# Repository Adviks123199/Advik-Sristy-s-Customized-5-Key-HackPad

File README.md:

# Advik-Sristy-s-Customized-5-Key-HackPad

I created this 5-key macropad, which features an ergonomic layout for fingers to reach the keys with ease. It also features a status LED, along with a capacitor.

Challenges:
I had a difficult time with the proportions and getting them right because KiCAD threw me off by so much.

Total time: 
It took me the entire long weekend to do this.

BOM:
-   x1 Microcontroller	Seeed Studio XIAO RP2040
-   x5 Switches	Cherry MX Style Switches
-   x1 SK6812 MINI LED
-   x5 Blank Keycaps	1u MX-compatible Keycaps
-   x4 M3x16 Bolt
-   x4 M3 Heatset
-   x1 roll of Solder(tin/lead)
-   x1 Soldering Iron

CASE TOP AND BOTTOM

SCHEMATIC                                          

PCB

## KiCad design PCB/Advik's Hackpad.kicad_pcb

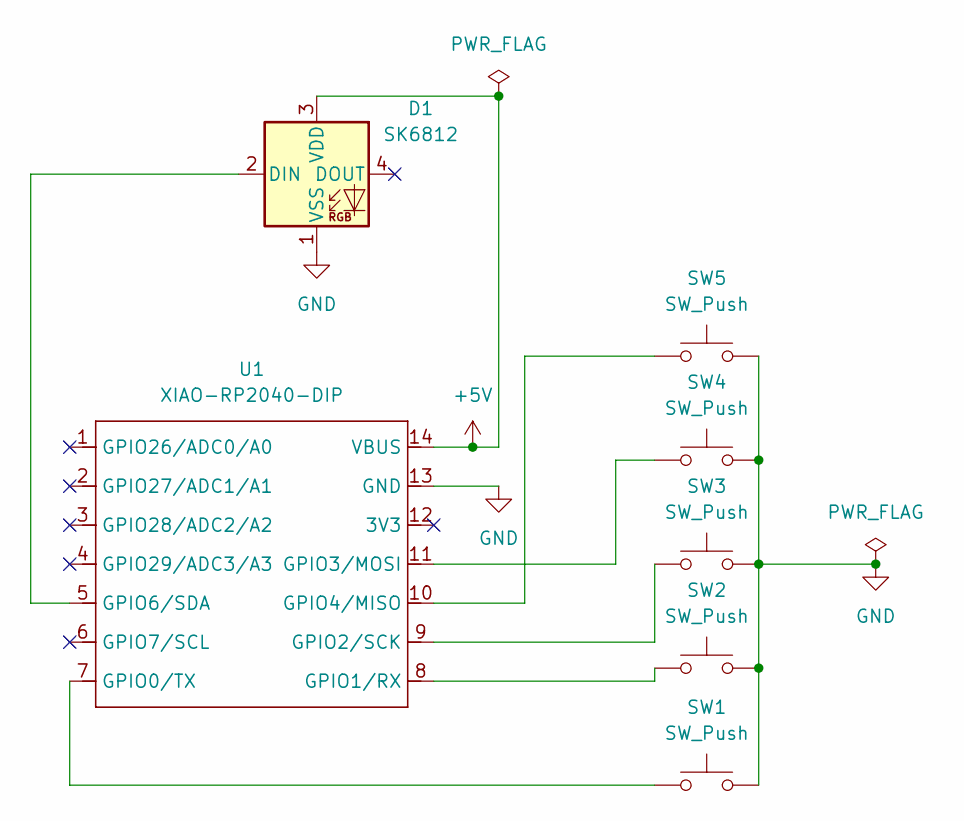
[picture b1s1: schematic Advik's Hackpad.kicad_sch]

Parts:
D1: SK6812; LED_SK6812MINI_PLCC4_3.5x3.5mm_P1.75mm
SW1, SW2, SW3, SW4, SW5: SW_Push; SW_Cherry_MX_1.00u_PCB
U1: XIAO-RP2040-DIP

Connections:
+5V: D1.3 (VDD), U1.14 (VBUS)
GND: D1.1 (VSS), SW1.2, SW2.2, SW3.2, SW4.2, SW5.2, U1.13 (GND)
unnamed: D1.2 (DIN), U1.5 (GPIO6/SDA)
unnamed: SW1.1, U1.7 (GPIO0/TX)
unnamed: SW2.1, U1.8 (GPIO1/RX)
unnamed: SW3.1, U1.9 (GPIO2/SCK)
unnamed: SW4.1, U1.11 (GPIO3/MOSI)
unnamed: SW5.1, U1.10 (GPIO4/MISO)

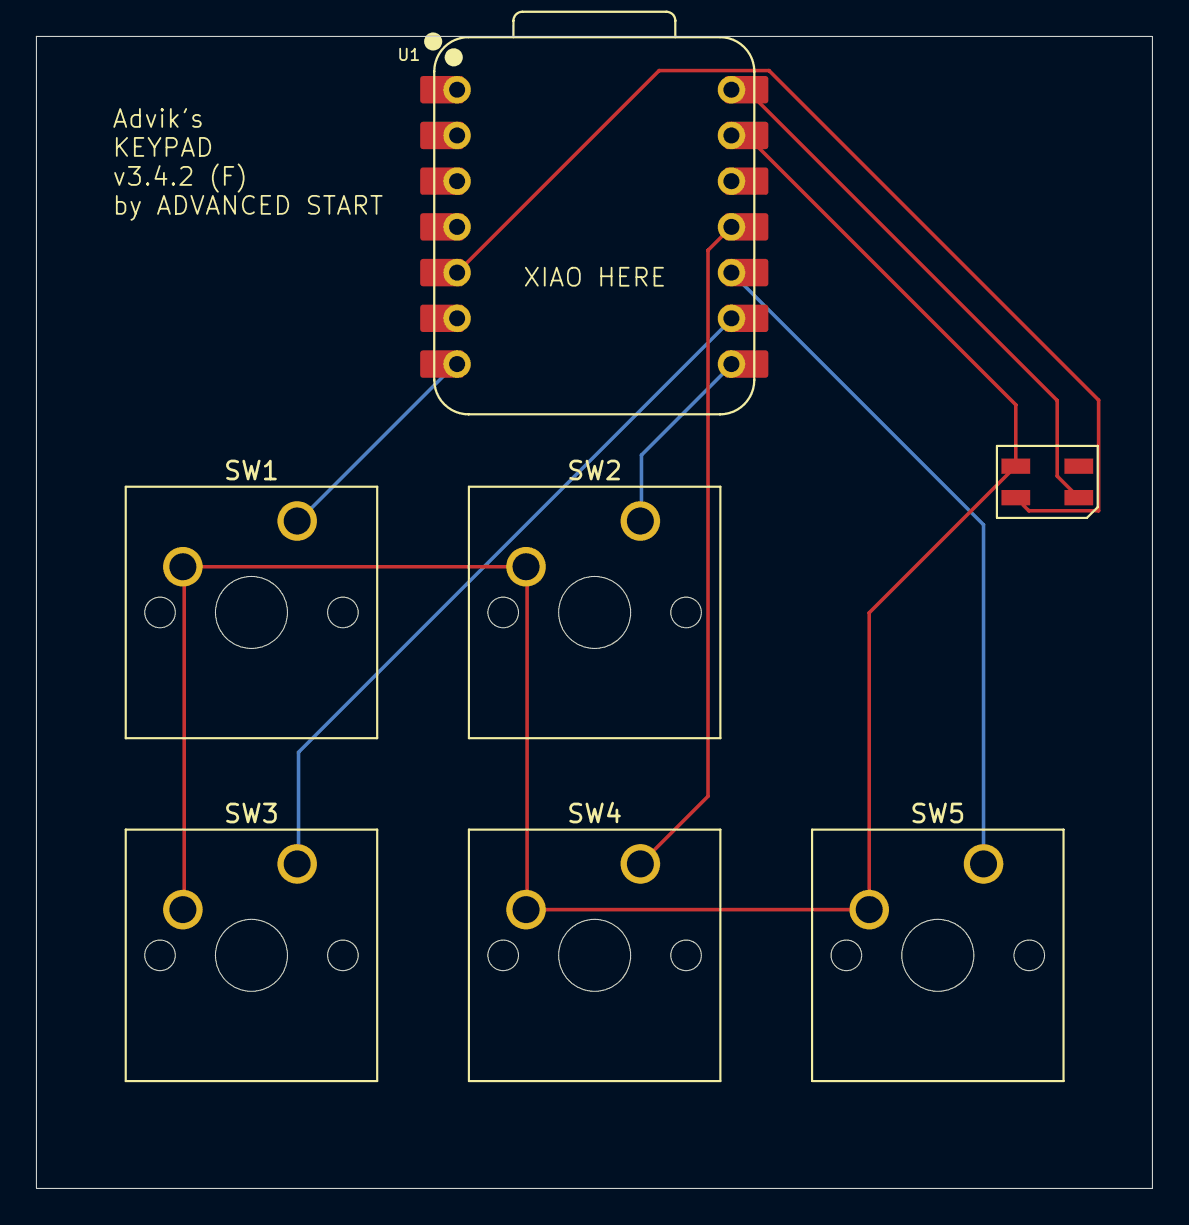
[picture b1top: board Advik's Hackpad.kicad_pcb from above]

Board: 2 copper layers, 62.0 x 64.0 mm, 7 parts (0 on the bottom side), 8 nets.

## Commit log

2026-01-19 Rename Advik's Hackpad.kicad_prl to PCB/Advik's Hackpad.kicad_prl
2026-01-19 Rename Advik's Hackpad.kicad_pro to PCB/Advik's Hackpad.kicad_pro
2026-01-19 Rename Advik's Hackpad Fully Assembled.step to CAD/Advik's Hackpad Fully Assembled.step
2026-01-19 Enhance README with project details and images
    Added detailed project description, challenges, total time, and bill of materials (BOM) for the 5-key macropad.
2026-01-19 Fix formatting of BOM section in README.md
2026-01-19 Update BOM in README.md
    Removed 0.1uF 0805 Ceramic Capacitor from BOM.
2026-01-19 Replace images in README with updated versions without the capacitor
    Updated schematic and PCB images in README.
